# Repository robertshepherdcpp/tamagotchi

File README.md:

# tamagotchi
luna-tamagotchi
my second project for fallout

**what the project is:**
- a custom tamagotchi consisting of a pcb designed in kiad and a case designed in the CAD software Fusion360
what the tamagotchi consists of:
- - a 3d case + lid
  - the pcb which consists of: XIAO-ESP32-C6, buzzer, rotary encoder, 4 buttons, and a 0.96" screen.

**why i chose to make with project (the inspiration/motivation):**
- as i am still new to hardware, i thought having a tutorial as a fallback for if i got stuck would be useful (avoid endless rabbit holes hhh). also i remember using a tamagotchi when i was younger and thought it was pretty cool
- so i decided to make a tamagotchi but to personalize it, so i made it of my friend luna.
- therefore as the firmware i planned to make it have many of the same interests/personality traits as my friend
- my mum had one of these when she was younger, and I thought it would be cool to make my own version and show it to her.

**how to use my project**
- first print off etc. the pcb and case. many different providers to do this.
- then to load the firmware (found in this respository), you can:
```
download the arduino IDE, install all the relevant libraries: Adafruit SSD1306 (by Adafruit), Adafruit GFX Library (by Adafruit). then
load up the xiao-esp32-c6 board. plug the project into your computer via usb, and press port on the arduino guide. as this project doesnt have a battery built
in, in order for this project to work it has to have a usb connected to it at all times.
for more help you can refer to these two guides:
https://fallout.hackclub.com/docs/guided-projects/tamagotchi-firmware
https://wiki.seeedstudio.com/xiao_esp32c6_getting_started/
```

**how the project works**
- the project is mainly just a tamogatchi with a few little changes.
- the pet has different characteristics, hunger, happiness, energy, age, intelligence
- there are 4 main states: `nap [SJ]`, `feed luosifen [LSF]`, `climb a mountain [CLMB]`, `wildcard [WLDCRD]`.
- nap: energy increases by 15 points, intelligence increases by 10 points.
- feed: hunger increases by 10 points (means it is getting less hungry), energy increases by 5 points
- play: happiness increases by 10 points, energy decreases by 5 points
- wildcard: this is where the rotary encoder comes into play, you select a random orientation on the tamogotchi which corresponds to a number
0-19 inclusive. a random number is then selected, if you pick that number, the one below it or above it, the pets happiness is doubled! however if you
dont guess correctly, its decreased by 15%!! are you willing to risk your pets happiness?
- all values apart from age are capped in the ranges 1 to 100.
- the aim to get all values as high as possible.
- this is all done behind the scenes with the pcb, controlled by the XIAO-ESP32-C6.

**how to use it?**
- after setting up the project (with the PCB and Case etc. all set up):
- this tamagotchi is your pet, you can feed it (luosifen), let it play (climb mountains), let it take a nap, and you can also go to a section called the wildcard
- this is where you pick a random number between 1 and 18 and if you get the number or one of the adjacent numbers, your pets happiness doubles! however if not the happiness is decreased by 15%.
- your ultimate goal is to keep your pet happy, healthy etc. by keeping the 4 stats variables high (intelligence, hunger, energy and happiness)

here are some images of the project:

(there are a few components missing in this image because the STEP files for them didnt load, however shouldnt have any effect when it comes to
the actual PCB fabrication.)

estimated costs (via uploading gerber files to jlcpcb):

[link](https://cart.jlcpcb.com/quote?stencilLayer=2&stencilWidth=100&stencilLength=100&stencilCounts=5&plateType=1&spm=Jlcpcb.Homepage.1010)

my zine:

The BOM (available in BOM.csv in this github repo):
aliexpress [link](https://www.aliexpress.com/p/shoppingcart/index.html?spm=a2g0o.tm1000056364.header.1.52471bf5lQ3z1L)

Total Cost: $27.44

the whole building process was documented on my youtube channel [here](https://www.youtube.com/@robertshepherdcpp)

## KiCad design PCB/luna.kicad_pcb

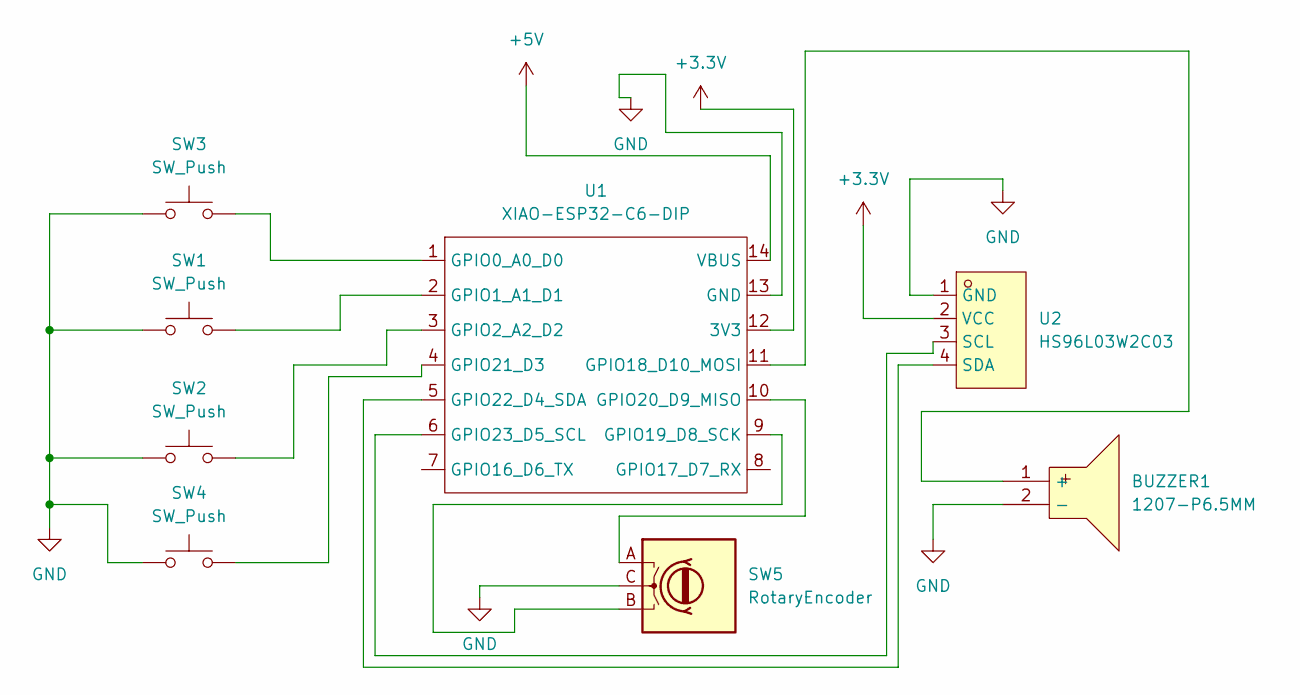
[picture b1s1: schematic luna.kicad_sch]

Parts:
BUZZER1: 1207-P6.5MM; BUZ-TH_BD12.5-P6.50-D1.4; MPN 1207-P6.5MM; LCSC Part C49246964
SW1, SW2, SW3, SW4: SW_Push; SW_Push_1P1T_NO_CK_KSC6xxG
SW5: RotaryEncoder; RotaryEncoder_Alps_EC11E-Switch_Vertical_H20mm
U1: XIAO-ESP32-C6-DIP
U2: HS96L03W2C03; OLED-TH_L27.8-W27.2-P2.54_C9900033791; MPN HS96L03W2C03; LCSC Part C5248080

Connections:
+3.3V: U1.12 (3V3), U2.2 (VCC)
+5V: U1.14 (VBUS)
GND: BUZZER1.2 (-), SW1.1, SW2.1, SW3.1, SW4.1, SW5.C, U1.13 (GND), U2.1 (GND)
unnamed: BUZZER1.1 (+), U1.11 (GPIO18_D10_MOSI)
unnamed: SW3.2, U1.1 (GPIO0_A0_D0)
unnamed: SW1.2, U1.2 (GPIO1_A1_D1)
unnamed: SW2.2, U1.3 (GPIO2_A2_D2)
unnamed: SW5.B, U1.9 (GPIO19_D8_SCK)
unnamed: SW5.A, U1.10 (GPIO20_D9_MISO)
unnamed: SW4.2, U1.4 (GPIO21_D3)
unnamed: U1.5 (GPIO22_D4_SDA), U2.4 (SDA)
unnamed: U1.6 (GPIO23_D5_SCL), U2.3 (SCL)

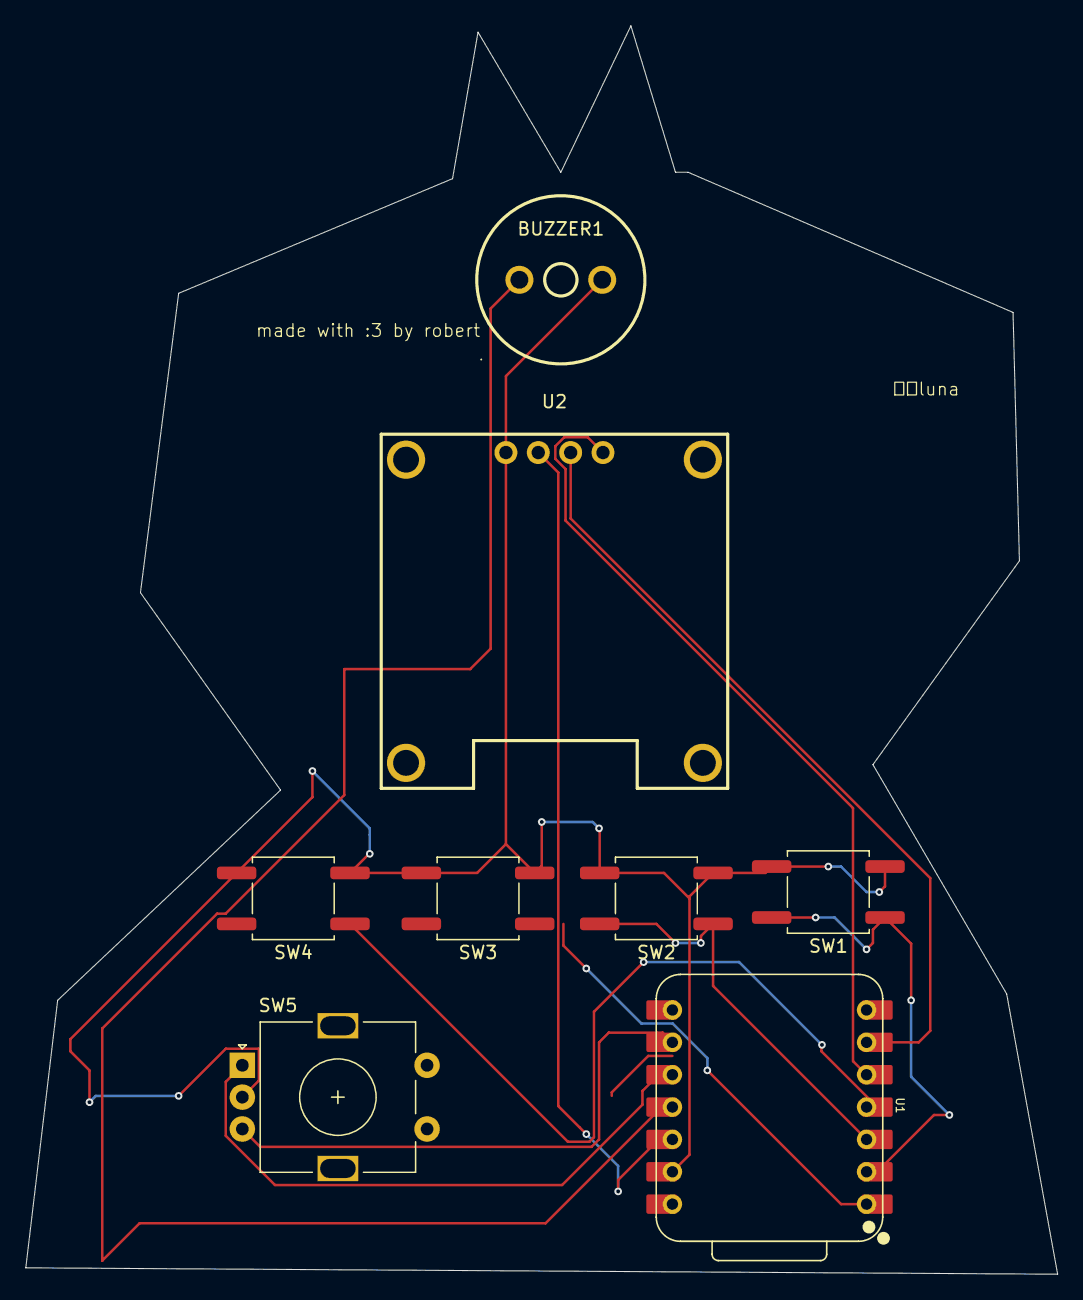
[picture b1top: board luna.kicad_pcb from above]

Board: 2 copper layers, 81.0 x 98.0 mm, 8 parts (0 on the bottom side), 11 nets.

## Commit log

2026-04-15 add the pcb files (still need the gerber files)
2026-04-15 add the gerber files
2026-04-15 Update README with estimated costs and images
    Added estimated costs section with images and links.
2026-04-15 Update README.md formatting
    Remove image tag and fix header formatting.
2026-04-15 Add TODO for BOM section in README
    Added a TODO note to write the BOM section in the README.
2026-04-17 Enhance README with usage and project functionality
    Updated usage instructions and project details in README.
2026-04-18 try add the firmware here...
2026-04-18 add zine
2026-04-18 Add BOM.csv with bill of materials details
2026-04-18 add updated zine
2026-04-18 Rename Untitled (1).pdf to zine.pdf
2026-04-18 Update README with new zine image and BOM details
    Added a new image to the zine section and updated the BOM information.
2026-04-18 Rename tamagotchi.ino.ino to firmware.ino
2026-04-18 Add YouTube link for building process documentation
    Added a link to the YouTube channel documenting the building process.
2026-04-18 Rename zine.pdf to zine/zine.pdf
2026-04-18 Rename BOM.csv to BOM/BOM.csv
2026-04-18 Rename Gerber files.zip to PCB/Gerber files.zip
2026-04-18 Rename luna.kicad_pcb to PCB/luna.kicad_pcb
2026-04-18 Rename luna.kicad_pro to PCB/luna.kicad_pro
2026-04-18 Rename luna.kicad_sch to PCB/luna.kicad_sch
2026-04-18 Rename firmware.ino to Firmware/firmware.ino
2026-04-18 Rename luna_2.f3d to CAD/luna_2.f3d
2026-04-18 Rename Untitled (2).pdf to Zine/zineV3.pdf
2026-04-18 Rename luna.step to PCB/luna.step
2026-04-18 Add usage instructions for tamagotchi project
    Added usage instructions for the tamagotchi project, detailing pet care activities and goals.
2026-04-18 Revise inspiration section in README.md
    Updated the inspiration section for clarity and added a personal anecdote.
2026-04-27 Update README with new images and BOM details
    Added a new image to the zine section and updated the BOM information.
2026-04-27 Rename Untitled (5).pdf to zine.pdf
2026-04-28 add the new zine
2026-04-28 Rename Untitled (6).pdf to zine.pdf
